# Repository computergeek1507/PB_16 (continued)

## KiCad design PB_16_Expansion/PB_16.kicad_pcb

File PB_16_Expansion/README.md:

# Copyright and Disclaimer
Copyright: Scott Hanson

This documentation describes Open Hardware and is licensed under the CERN Open Hardware License Version 2 - Strongly Reciprocal. (CERN-OHL-S)

You may redistribute and modify this documentation under the terms of the CERN OHL-S-v2 (https://ohwr.org/cern_ohl_s_v2.txt). This documentation is distributed WITHOUT ANY EXPRESS OR IMPLIED WARRANTY, INCLUDING OF MERCHANTABILITY, SATISFACTORY QUALITY AND FITNESS FOR A PARTICULAR PURPOSE. Please see the CERN OHL v2-S for applicable conditions

**Under CERN OHL-S-v2, derivative work must be publicly released as defined in subsection 3.3**

# PB 16 Expansion

The PB16 Expansion is a compact version of the PB16 with only two Expansion Headers. It can be used with any PB16 Family Expansion or Falcon Expansion Boards. There is also an optional [serial breakout board](../PB_16_E682_Serial/README.md) for DMX capability. All the design files are open source and available on github.

## [Part BOM](https://github.com/computergeek1507/PB_16/raw/master/PB_16_Expansion/PB_16.csv)

## [Interactive BOM](https://computergeek1507.github.io/PB_16/PB_16_Expansion/bom/ibom)

----
## Changelog

v5
----
* 2026-02-20
* Add Different Output
* Switched Expansion Header to 24pin Falcon V4 pinout.
* Switched to PB16v2 pinout, use PB16v2 EEPROM

v4
----
* 2022-08-13
* Updated 5V regulator to "Universal" footprint to support different regulators.
* Added Logo

v3
----
* 2020-05-06
* Wiring Routing Updates.

v2
----
* 2020-01-02
* Add Serial Output Header.

v1
----
* 2019-12-31
* First Version.

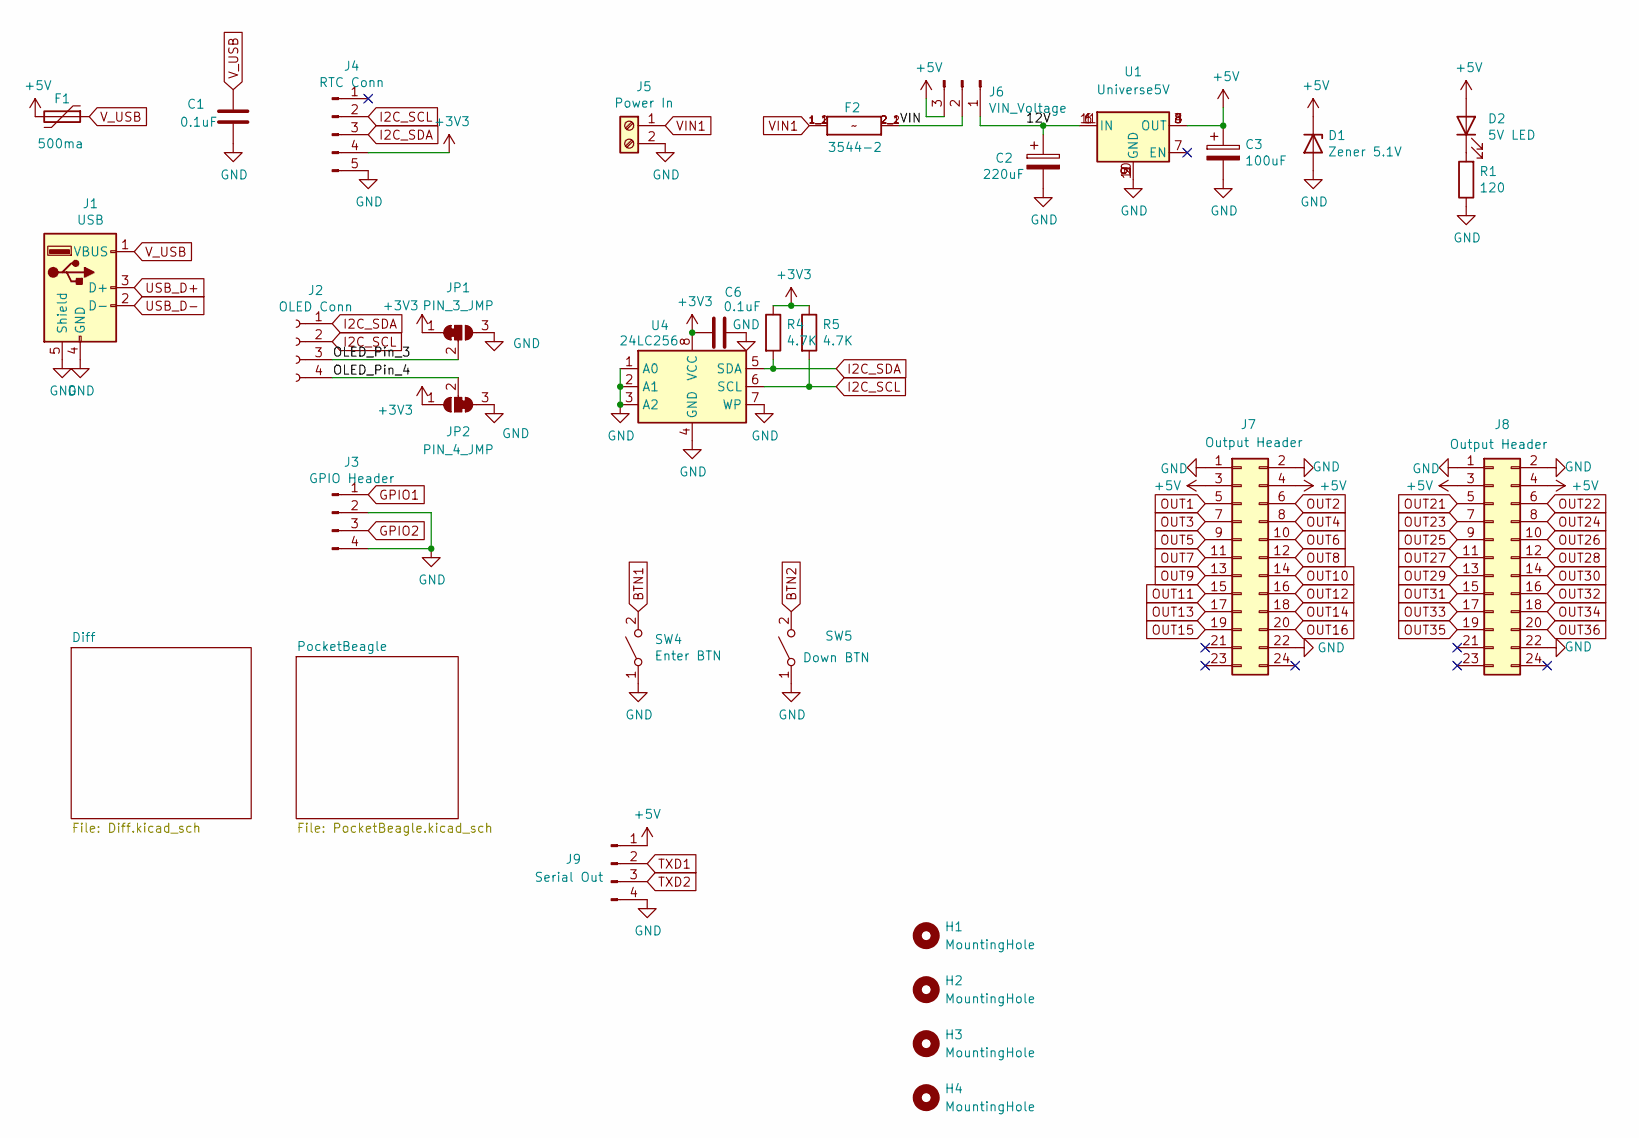
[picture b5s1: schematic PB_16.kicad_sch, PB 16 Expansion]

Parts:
C1, C6: 0.1uF; C_Rect_L7.0mm_W2.0mm_P5.00mm; MPN SR215C104KARTR1; Digi-Key_PN 478-7336-1-ND
C2: 220uF; CP_Radial_D10.0mm_P5.00mm; MPN ECA-1HM221; Digi-Key_PN P5183-ND
C3: 100uF; CP_Radial_D5.0mm_P2.00mm; MPN 16ZLH100MEFC5X11; Digi-Key_PN 1189-1148-ND
D1: Zener 5.1V; D_5W_P10.16mm_Horizontal; MPN 1N5338BRLG; Digi-Key_PN 1N5338BRLGOSCT-ND
D2: 5V LED; LED_D3.0mm; MPN WP3A8GD; Digi-Key_PN 754-1217-ND
F1: 500ma; Fuse_BelFuse_0ZRE0005FF_L8.3mm_W3.8mm; MPN RXEF050-2; Digi-Key_PN RXEF050-2HFCT-ND
F2: 3544-2; FUSE_3544-2; MPN 3544-2; Digi-Key_PN 36-3544-2-ND
H1, H2, H3, H4: MountingHole; MountingHole_3.7mm
J1: USB; USB_A_Molex_105057_Vertical; MPN 1050570001; Digi-Key_PN WM8672-ND
J2: OLED Conn; PinSocket_1x04_P2.54mm_Vertical; MPN PPTC041LFBN-RC; Digi-Key_PN S7002-ND
J3: GPIO Header; JST_XH_B4B-XH-A_1x04_P2.50mm_Vertical; MPN B4B-XH-A(LF)(SN); Digi-Key_PN 455-2249-ND
J4: RTC Conn; PinHeader_1x05_P2.54mm_Vertical; MPN 61300511121; Digi-Key_PN 732-5318-ND
J5: Power In; PHOENIX_MKDS1_2-3.81; MPN 1727010; Digi-Key_PN 277-1947-ND
J6: VIN_Voltage; PinHeader_1x03_P2.54mm_Vertical; MPN 61300311121; Digi-Key_PN 732-5316-ND
J7, J8: Output Header; IDC-Header_2x12_P2.54mm_Vertical; MPN 61202421621; Digi-Key_PN 732-5398-ND
J9: Serial Out; PinHeader_1x04_P2.54mm_Vertical; MPN 61300411121; Digi-Key_PN 732-5317-ND
JP1: PIN_3_JMP; SolderJumper-3_P1mm_Bridged12
JP2: PIN_4_JMP; SolderJumper-3_P1mm_Bridged23
R1: 120; R_Axial_DIN0207_L6.3mm_D2.5mm_P7.62mm_Horizontal; MPN CF14JT120R; Digi-Key_PN CF14JT120RCT-ND
R4, R5: 4.7K; R_Axial_DIN0207_L6.3mm_D2.5mm_P7.62mm_Horizontal; MPN CF14JT4K70; Digi-Key_PN CF14JT4K70CT-ND
SW4: Enter BTN; SW_PUSH_6mm; MPN 1825910-6; Digi-Key_PN 450-1650-ND
SW5: Down BTN; SW_PUSH_6mm; MPN 1825910-6; Digi-Key_PN 450-1650-ND
U1: Universe5V; Universal_5V_Horizontal; MPN OKI-78SR-5/1.5-W36H-C; Digi-Key_PN 811-2692-ND
U4: 24LC256; DIP-8_W7.62mm; MPN FT24C256A-UDR-B; Digi-Key_PN 1219-1052-ND

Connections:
+3V3: C6.2, J4.4, JP1.1 (A), JP2.1 (A), R4.1, R5.1, U4.8 (VCC); also elsewhere on the board
+5V: C3.1, D1.1 (K), D2.2 (A), F1.2, J6.3, J7.3, J7.4, J8.3, J8.4, J9.1, U1.3 (OUT), U1.4 (OUT), U1.8 (OUT); also elsewhere on the board
/12V: C2.1, J6.1, U1.1 (IN), U1.6 (IN), U1.11 (IN)
/OLED_Pin_3: J2.3, JP1.2 (C)
/OLED_Pin_4: J2.4, JP2.2 (C)
/VIN: F2.2_1 (2), F2.2_2 (2), J6.2
BTN1: SW4.2 (B); also elsewhere on the board
BTN2: SW5.2 (B); also elsewhere on the board
GND: C1.2, C2.2, C3.2, C6.1, D1.2 (A), J1.4 (GND), J1.5 (Shield), J3.2, J3.4, J4.5, J5.2, J7.1, J7.2, J7.22, J8.1, J8.2, J8.22, J9.4, JP1.3 (B), JP2.3 (B), R1.1, SW4.1 (A), SW5.1 (A), U1.2 (GND), U1.5 (GND), U1.9 (GND), U1.10 (GND), U4.1 (A0), U4.2 (A1), U4.3 (A2), U4.4 (GND), U4.7 (WP); also elsewhere on the board
GPIO1: J3.1; also elsewhere on the board
GPIO2: J3.3; also elsewhere on the board
I2C_SCL: J2.2, J4.2, R5.2, U4.6 (SCL); also elsewhere on the board
I2C_SDA: J2.1, J4.3, R4.2, U4.5 (SDA); also elsewhere on the board
unnamed: D2.1 (K), R1.2
OUT1: J7.5; also elsewhere on the board
OUT2: J7.6; also elsewhere on the board
OUT3: J7.7; also elsewhere on the board
OUT4: J7.8; also elsewhere on the board
OUT5: J7.9; also elsewhere on the board
OUT6: J7.10; also elsewhere on the board
OUT7: J7.11; also elsewhere on the board
OUT8: J7.12; also elsewhere on the board
OUT9: J7.13; also elsewhere on the board
OUT10: J7.14; also elsewhere on the board
OUT11: J7.15; also elsewhere on the board
OUT12: J7.16; also elsewhere on the board
OUT13: J7.17; also elsewhere on the board
OUT14: J7.18; also elsewhere on the board
OUT15: J7.19; also elsewhere on the board
OUT16: J7.20; also elsewhere on the board
OUT21: J8.5; also elsewhere on the board
OUT22: J8.6; also elsewhere on the board
OUT23: J8.7; also elsewhere on the board
OUT24: J8.8; also elsewhere on the board
OUT25: J8.9; also elsewhere on the board
OUT26: J8.10; also elsewhere on the board
OUT27: J8.11; also elsewhere on the board
OUT28: J8.12; also elsewhere on the board
OUT29: J8.13; also elsewhere on the board
OUT30: J8.14; also elsewhere on the board
OUT31: J8.15; also elsewhere on the board
OUT32: J8.16; also elsewhere on the board
OUT33: J8.17; also elsewhere on the board
OUT34: J8.18; also elsewhere on the board
OUT35: J8.19; also elsewhere on the board
OUT36: J8.20; also elsewhere on the board
TXD1: J9.2; also elsewhere on the board
TXD2: J9.3; also elsewhere on the board
USB_D+: J1.3 (D+); also elsewhere on the board
USB_D-: J1.2 (D-); also elsewhere on the board
VIN1: F2.1_1 (1), F2.1_2 (1), J5.1
V_USB: C1.1, F1.1, J1.1 (VBUS); also elsewhere on the board

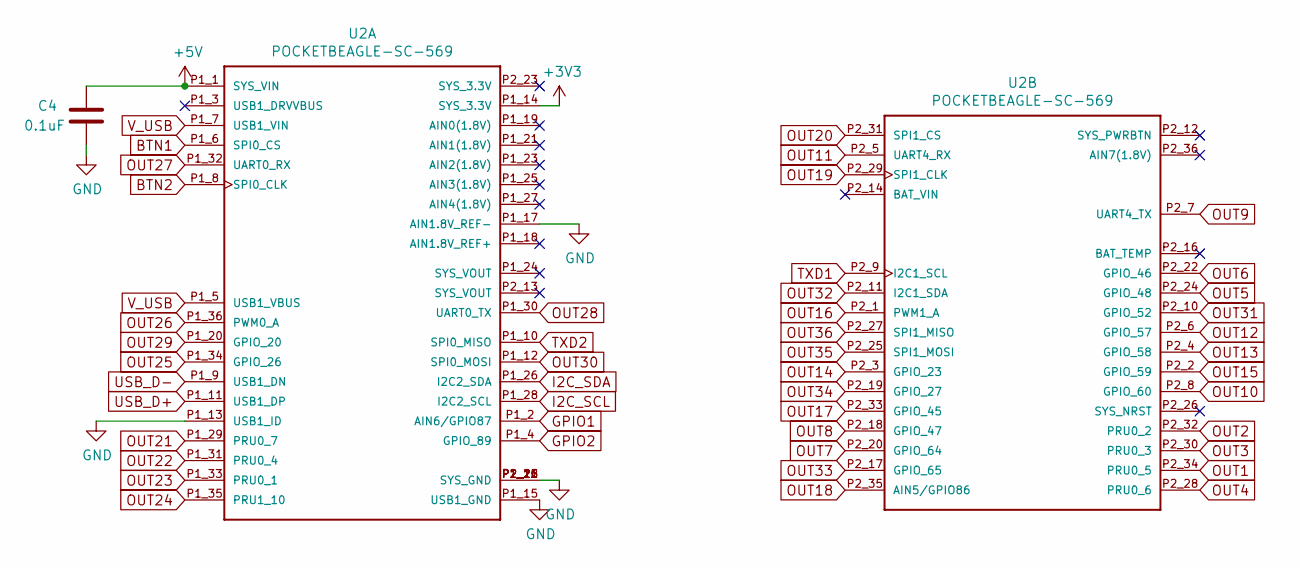
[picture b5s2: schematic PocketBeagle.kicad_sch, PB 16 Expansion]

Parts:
C4: 0.1uF; C_Rect_L7.0mm_W2.0mm_P5.00mm; MPN SR215C104KARTR1; Digi-Key_PN 478-7336-1-ND
U2: POCKETBEAGLE-SC-569; BEAGLE_POCKETBEAGLE-SC-569; MPN POCKETBEAGLE-SC-569; Digi-Key_PN POCKETBEAGLE-SC-569-ND

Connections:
+3V3: U2.P1_14 (SYS_3.3V); also elsewhere on the board
+5V: C4.1, U2.P1_1 (SYS_VIN); also elsewhere on the board
BTN1: U2.P1_6 (SPI0_CS); also elsewhere on the board
BTN2: U2.P1_8 (SPI0_CLK); also elsewhere on the board
GND: C4.2, U2.P1_13 (USB1_ID), U2.P1_15 (USB1_GND), U2.P1_16 (SYS_GND), U2.P1_17 (AIN1.8V_REF-), U2.P1_22 (SYS_GND), U2.P2_15 (SYS_GND), U2.P2_21 (SYS_GND); also elsewhere on the board
GPIO1: U2.P1_2 (AIN6/GPIO87); also elsewhere on the board
GPIO2: U2.P1_4 (GPIO_89); also elsewhere on the board
I2C_SCL: U2.P1_28 (I2C2_SCL); also elsewhere on the board
I2C_SDA: U2.P1_26 (I2C2_SDA); also elsewhere on the board
OUT1: U2.P2_34 (PRU0_5); also elsewhere on the board
OUT2: U2.P2_32 (PRU0_2); also elsewhere on the board
OUT3: U2.P2_30 (PRU0_3); also elsewhere on the board
OUT4: U2.P2_28 (PRU0_6); also elsewhere on the board
OUT5: U2.P2_24 (GPIO_48); also elsewhere on the board
OUT6: U2.P2_22 (GPIO_46); also elsewhere on the board
OUT7: U2.P2_20 (GPIO_64); also elsewhere on the board
OUT8: U2.P2_18 (GPIO_47); also elsewhere on the board
OUT9: U2.P2_7 (UART4_TX); also elsewhere on the board
OUT10: U2.P2_8 (GPIO_60); also elsewhere on the board
OUT11: U2.P2_5 (UART4_RX); also elsewhere on the board
OUT12: U2.P2_6 (GPIO_57); also elsewhere on the board
OUT13: U2.P2_4 (GPIO_58); also elsewhere on the board
OUT14: U2.P2_3 (GPIO_23); also elsewhere on the board
OUT15: U2.P2_2 (GPIO_59); also elsewhere on the board
OUT16: U2.P2_1 (PWM1_A); also elsewhere on the board
OUT17: U2.P2_33 (GPIO_45); also elsewhere on the board
OUT18: U2.P2_35 (AIN5/GPIO86); also elsewhere on the board
OUT19: U2.P2_29 (SPI1_CLK); also elsewhere on the board
OUT20: U2.P2_31 (SPI1_CS); also elsewhere on the board
OUT21: U2.P1_29 (PRU0_7); also elsewhere on the board
OUT22: U2.P1_31 (PRU0_4); also elsewhere on the board
OUT23: U2.P1_33 (PRU0_1); also elsewhere on the board
OUT24: U2.P1_35 (PRU1_10); also elsewhere on the board
OUT25: U2.P1_34 (GPIO_26); also elsewhere on the board
OUT26: U2.P1_36 (PWM0_A); also elsewhere on the board
OUT27: U2.P1_32 (UART0_RX); also elsewhere on the board
OUT28: U2.P1_30 (UART0_TX); also elsewhere on the board
OUT29: U2.P1_20 (GPIO_20); also elsewhere on the board
OUT30: U2.P1_12 (SPI0_MOSI); also elsewhere on the board
OUT31: U2.P2_10 (GPIO_52); also elsewhere on the board
OUT32: U2.P2_11 (I2C1_SDA); also elsewhere on the board
OUT33: U2.P2_17 (GPIO_65); also elsewhere on the board
OUT34: U2.P2_19 (GPIO_27); also elsewhere on the board
OUT35: U2.P2_25 (SPI1_MOSI); also elsewhere on the board
OUT36: U2.P2_27 (SPI1_MISO); also elsewhere on the board
TXD1: U2.P2_9 (I2C1_SCL); also elsewhere on the board
TXD2: U2.P1_10 (SPI0_MISO); also elsewhere on the board
USB_D+: U2.P1_11 (USB1_DP); also elsewhere on the board
USB_D-: U2.P1_9 (USB1_DN); also elsewhere on the board
V_USB: U2.P1_5 (USB1_VBUS), U2.P1_7 (USB1_VIN); also elsewhere on the board

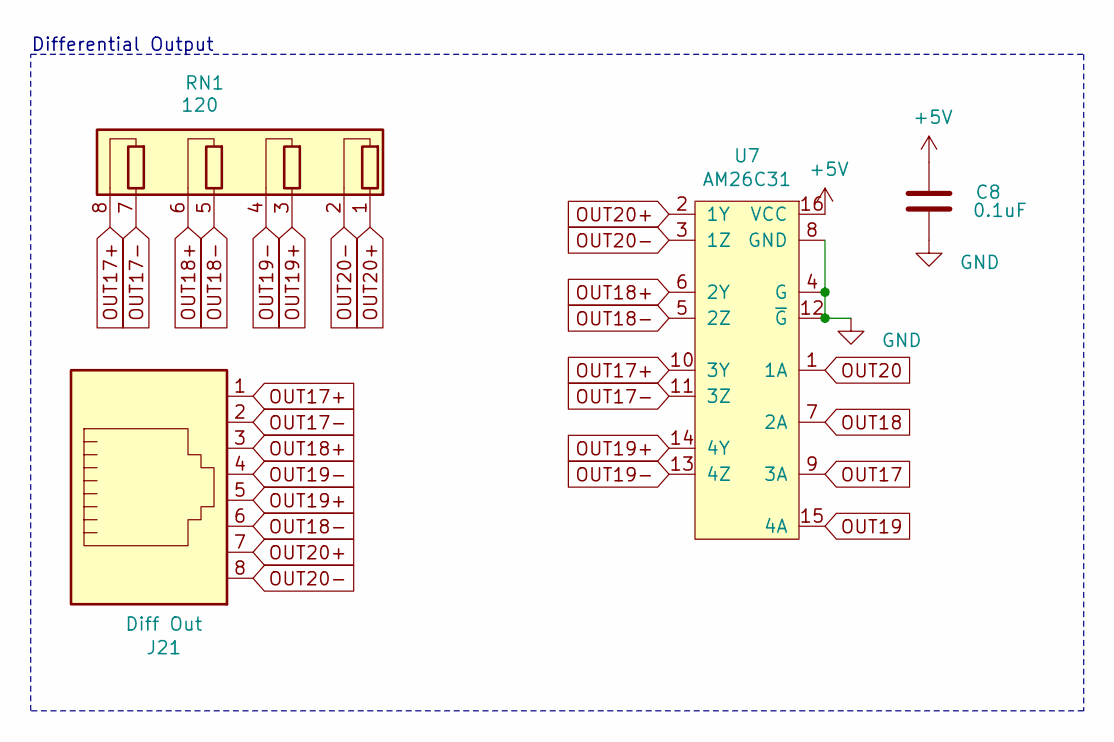
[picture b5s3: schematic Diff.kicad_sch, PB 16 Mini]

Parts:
C8: 0.1uF; C_Rect_L7.0mm_W2.0mm_P5.00mm; MPN SR215C104KARTR1; Digi-Key_PN 478-7336-1-ND
J21: Diff Out; RJ45_Amphenol_54602-x08_Horizontal; MPN X05ADIWA1DY1022; Digi-Key_PN AE10392-ND
RN1: 120; R_Array_SIP8; MPN 4608X-102-121LF; Digikey PN 4608X-2-121LF-ND
U7: AM26C31; DIP-16_W7.62mm; MPN AM26C31IN; Farnell 4975637

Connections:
+5V: C8.1, U7.16 (VCC); also elsewhere on the board
GND: C8.2, U7.4 (G), U7.8 (GND), U7.12 (~G); also elsewhere on the board
OUT17: U7.9 (3A); also elsewhere on the board
OUT17+: J21.1, RN1.8 (R4.2), U7.10 (3Y)
OUT17-: J21.2, RN1.7 (R4.1), U7.11 (3Z)
OUT18: U7.7 (2A); also elsewhere on the board
OUT18+: J21.3, RN1.6 (R3.2), U7.6 (2Y)
OUT18-: J21.6, RN1.5 (R3.1), U7.5 (2Z)
OUT19: U7.15 (4A); also elsewhere on the board
OUT19+: J21.5, RN1.3 (R2.1), U7.14 (4Y)
OUT19-: J21.4, RN1.4 (R2.2), U7.13 (4Z)
OUT20: U7.1 (1A); also elsewhere on the board
OUT20+: J21.7, RN1.1 (R1.1), U7.2 (1Y)
OUT20-: J21.8, RN1.2 (R1.2), U7.3 (1Z)

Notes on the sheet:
Differential Output

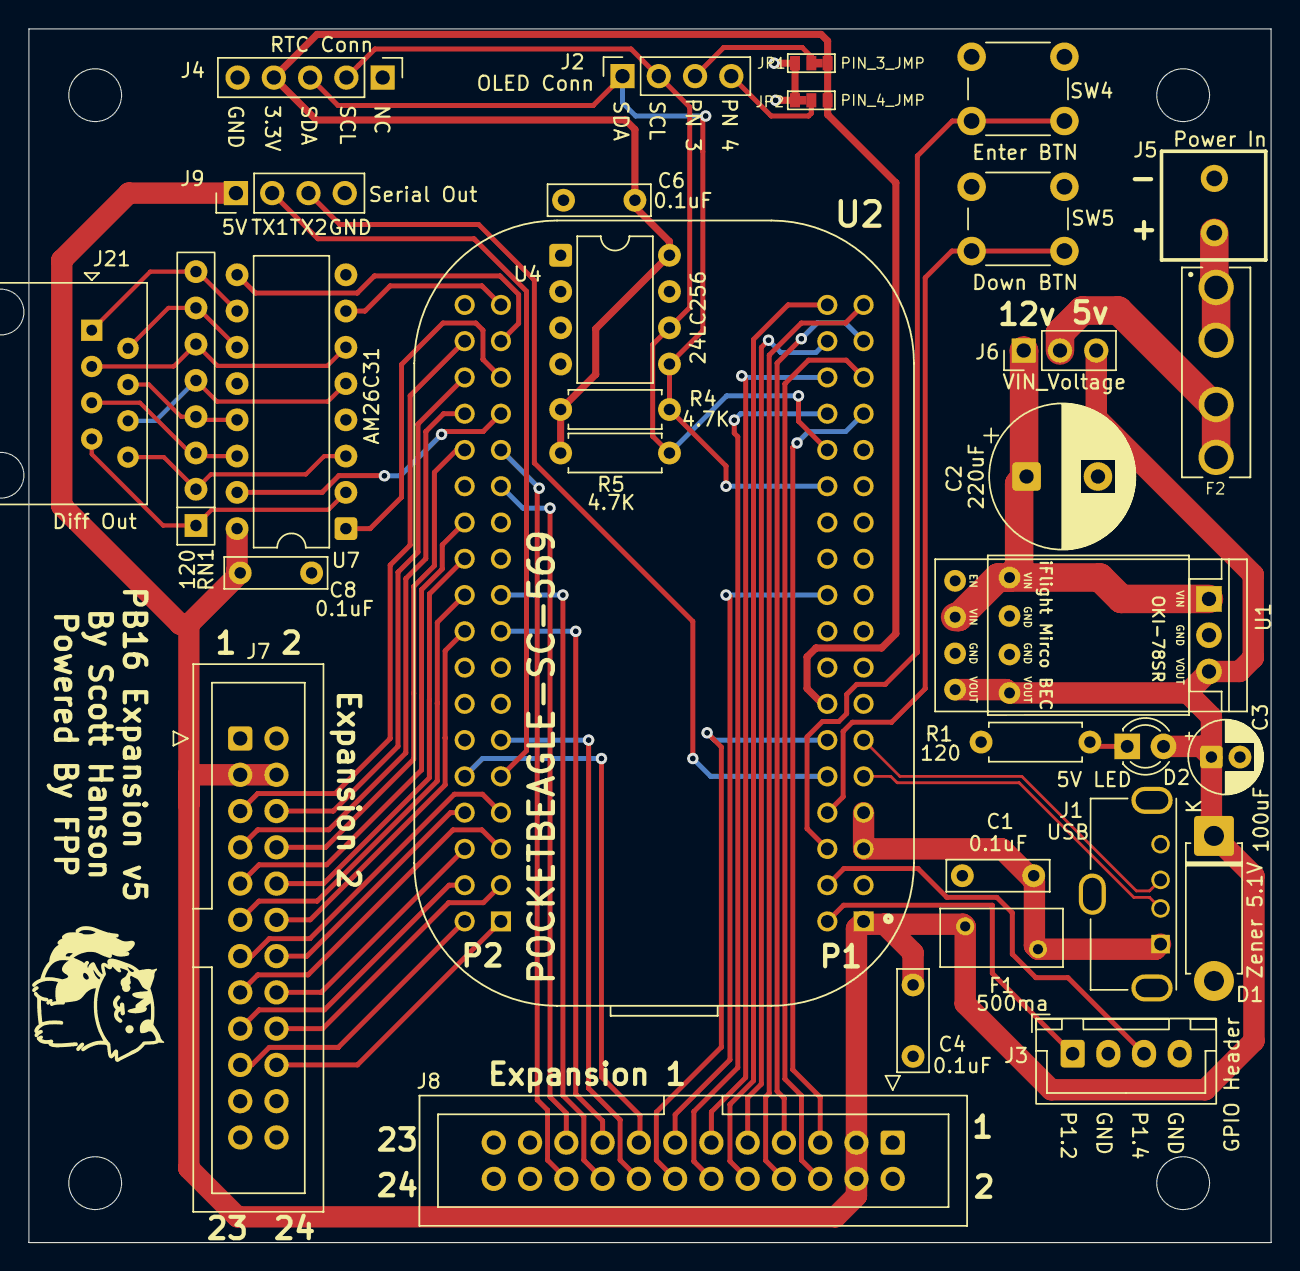
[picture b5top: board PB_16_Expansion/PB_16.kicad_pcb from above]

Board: 2 copper layers, 87.0 x 85.0 mm, 36 parts (0 on the bottom side), 64 nets.

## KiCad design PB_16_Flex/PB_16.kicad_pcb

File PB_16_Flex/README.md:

# Copyright and Disclaimer
Copyright: Scott Hanson

This documentation describes Open Hardware and is licensed under the CERN Open Hardware License Version 2 - Strongly Reciprocal. (CERN-OHL-S)

You may redistribute and modify this documentation under the terms of the CERN OHL-S-v2 (https://ohwr.org/cern_ohl_s_v2.txt). This documentation is distributed WITHOUT ANY EXPRESS OR IMPLIED WARRANTY, INCLUDING OF MERCHANTABILITY, SATISFACTORY QUALITY AND FITNESS FOR A PARTICULAR PURPOSE. Please see the CERN OHL v2-S for applicable conditions

**Under CERN OHL-S-v2, derivative work must be publicly released as defined in subsection 3.3**

# PB 16 Flex

The PB16 Flex is a version of the PB16 for the HolidayCoro Flex System. It can be used with only two flex boards, 32 outputs. All the design files are open source and available on github.

## [Part BOM](https://github.com/computergeek1507/PB_16/raw/master/PB_16_Flex/PB_16_Flex_BOM.ods)

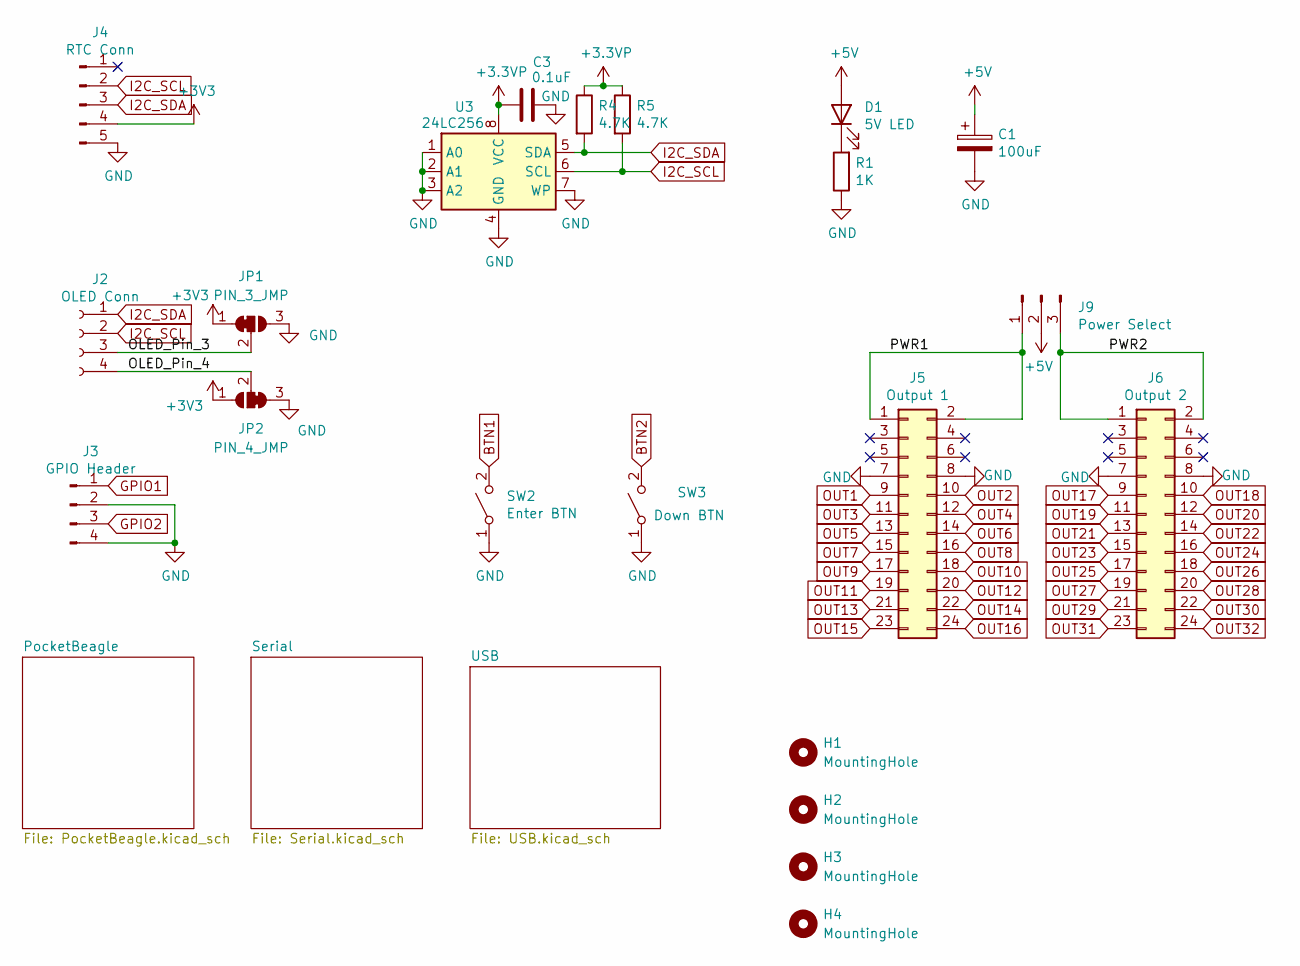
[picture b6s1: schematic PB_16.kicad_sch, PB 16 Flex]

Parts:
C1: 100uF; CP_Elec_6.3x5.4_Nichicon; MPN UWX1C101MCL1GB; Digi-Key_PN 493-2105-1-ND
C3: 0.1uF; C_0805_2012Metric; MPN CL21F104ZBCNNNC; Digi-Key_PN 1276-1007-1-ND
D1: 5V LED; LED_0805_2012Metric_Pad1.15x1.40mm_HandSolder; MPN LTST-C171GKT; Digi-Key_PN 160-1423-1-ND
H1, H2, H3, H4: MountingHole; MountingHole_3.7mm
J2: OLED Conn; PinSocket_1x04_P2.54mm_Vertical; MPN PPTC041LFBN-RC; Digi-Key_PN S7002-ND
J3: GPIO Header; JST_XH_B4B-XH-A_1x04_P2.50mm_Vertical; MPN B4B-XH-A(LF)(SN); Digi-Key_PN 455-2249-ND
J4: RTC Conn; PinHeader_1x05_P2.54mm_Vertical; MPN 61300511121; Digi-Key_PN 732-5318-ND
J5: Output 1; OST_302-S241; MPN 302-S241; Digi-Key_PN ED10525-ND
J6: Output 2; OST_302-S241; MPN 302-S241; Digi-Key_PN ED10525-ND
J9: Power Select; PinHeader_1x03_P2.54mm_Vertical; MPN 61300311121; Digi-Key_PN 732-5316-ND
JP1: PIN_3_JMP; SolderJumper-3_P1mm_Bridged12
JP2: PIN_4_JMP; SolderJumper-3_P1mm_Bridged23
R1: 1K; R_0805_2012Metric; MPN RC0805FR-071KL; Digi-Key_PN 311-1.00KCRCT-ND
R4, R5: 4.7K; R_0805_2012Metric; MPN RC0805JR-074K7L; Digi-Key_PN 311-4.7KARCT-ND
SW2: Enter BTN; SW_PUSH_6mm; MPN 1825910-6; Digi-Key_PN 450-1650-ND
SW3: Down BTN; SW_PUSH_6mm; MPN 1825910-6; Digi-Key_PN 450-1650-ND
U3: 24LC256; SOIC-8_3.9x4.9mm_P1.27mm; MPN 24LC256T-I/SN; Digi-Key_PN 24LC256T-I/SNCT-ND

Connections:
+3.3VP: C3.2, R4.1, R5.1, U3.8 (VCC); also elsewhere on the board
+3V3: J4.4, JP1.1 (A), JP2.1 (A); also elsewhere on the board
+5V: C1.1, D1.2 (A), J9.2; also elsewhere on the board
/OLED_Pin_3: J2.3, JP1.2 (C)
/OLED_Pin_4: J2.4, JP2.2 (C)
/PWR1: J5.1, J5.2, J9.1
/PWR2: J6.1, J6.2, J9.3
BTN1: SW2.2 (B); also elsewhere on the board
BTN2: SW3.2 (B); also elsewhere on the board
GND: C1.2, C3.1, J3.2, J3.4, J4.5, J5.7, J5.8, J6.7, J6.8, JP1.3 (B), JP2.3 (B), R1.1, SW2.1 (A), SW3.1 (A), U3.1 (A0), U3.2 (A1), U3.3 (A2), U3.4 (GND), U3.7 (WP); also elsewhere on the board
GPIO1: J3.1; also elsewhere on the board
GPIO2: J3.3; also elsewhere on the board
I2C_SCL: J2.2, J4.2, R5.2, U3.6 (SCL); also elsewhere on the board
I2C_SDA: J2.1, J4.3, R4.2, U3.5 (SDA); also elsewhere on the board
unnamed: D1.1 (K), R1.2
OUT1: J5.9; also elsewhere on the board
OUT2: J5.10; also elsewhere on the board
OUT3: J5.11; also elsewhere on the board
OUT4: J5.12; also elsewhere on the board
OUT5: J5.13; also elsewhere on the board
OUT6: J5.14; also elsewhere on the board
OUT7: J5.15; also elsewhere on the board
OUT8: J5.16; also elsewhere on the board
OUT9: J5.17; also elsewhere on the board
OUT10: J5.18; also elsewhere on the board
OUT11: J5.19; also elsewhere on the board
OUT12: J5.20; also elsewhere on the board
OUT13: J5.21; also elsewhere on the board
OUT14: J5.22; also elsewhere on the board
OUT15: J5.23; also elsewhere on the board
OUT16: J5.24; also elsewhere on the board
OUT17: J6.9; also elsewhere on the board
OUT18: J6.10; also elsewhere on the board
OUT19: J6.11; also elsewhere on the board
OUT20: J6.12; also elsewhere on the board
OUT21: J6.13; also elsewhere on the board
OUT22: J6.14; also elsewhere on the board
OUT23: J6.15; also elsewhere on the board
OUT24: J6.16; also elsewhere on the board
OUT25: J6.17; also elsewhere on the board
OUT26: J6.18; also elsewhere on the board
OUT27: J6.19; also elsewhere on the board
OUT28: J6.20; also elsewhere on the board
OUT29: J6.21; also elsewhere on the board
OUT30: J6.22; also elsewhere on the board
OUT31: J6.23; also elsewhere on the board
OUT32: J6.24; also elsewhere on the board

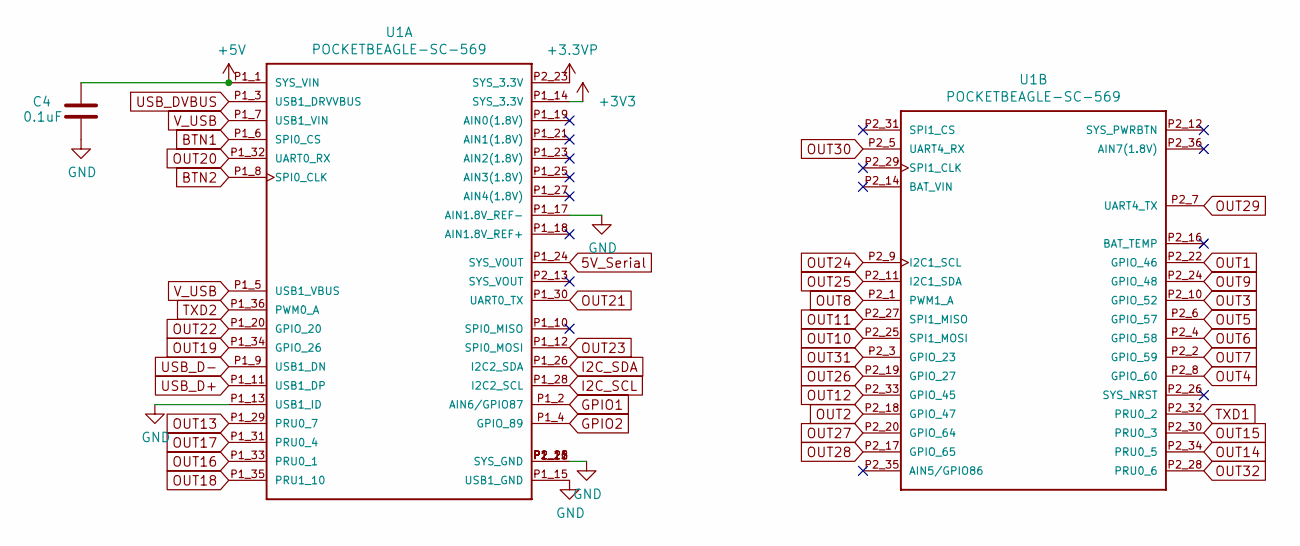
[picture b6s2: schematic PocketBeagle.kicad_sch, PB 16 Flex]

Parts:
C4: 0.1uF; C_0805_2012Metric; MPN CL21F104ZBCNNNC; Digi-Key_PN 1276-1007-1-ND
U1: POCKETBEAGLE-SC-569; BEAGLE_POCKETBEAGLE-SC-569; MPN POCKETBEAGLE-SC-569; Digi-Key_PN POCKETBEAGLE-SC-569-ND

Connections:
5V_Serial: U1.P1_24 (SYS_VOUT); also elsewhere on the board
+3.3VP: U1.P2_23 (SYS_3.3V); also elsewhere on the board
+3V3: U1.P1_14 (SYS_3.3V); also elsewhere on the board
+5V: C4.1, U1.P1_1 (SYS_VIN); also elsewhere on the board
BTN1: U1.P1_6 (SPI0_CS); also elsewhere on the board
BTN2: U1.P1_8 (SPI0_CLK); also elsewhere on the board
GND: C4.2, U1.P1_13 (USB1_ID), U1.P1_15 (USB1_GND), U1.P1_16 (SYS_GND), U1.P1_17 (AIN1.8V_REF-), U1.P1_22 (SYS_GND), U1.P2_15 (SYS_GND), U1.P2_21 (SYS_GND); also elsewhere on the board
GPIO1: U1.P1_2 (AIN6/GPIO87); also elsewhere on the board
GPIO2: U1.P1_4 (GPIO_89); also elsewhere on the board
I2C_SCL: U1.P1_28 (I2C2_SCL); also elsewhere on the board
I2C_SDA: U1.P1_26 (I2C2_SDA); also elsewhere on the board
OUT1: U1.P2_22 (GPIO_46); also elsewhere on the board
OUT2: U1.P2_18 (GPIO_47); also elsewhere on the board
OUT3: U1.P2_10 (GPIO_52); also elsewhere on the board
OUT4: U1.P2_8 (GPIO_60); also elsewhere on the board
OUT5: U1.P2_6 (GPIO_57); also elsewhere on the board
OUT6: U1.P2_4 (GPIO_58); also elsewhere on the board
OUT7: U1.P2_2 (GPIO_59); also elsewhere on the board
OUT8: U1.P2_1 (PWM1_A); also elsewhere on the board
OUT9: U1.P2_24 (GPIO_48); also elsewhere on the board
OUT10: U1.P2_25 (SPI1_MOSI); also elsewhere on the board
OUT11: U1.P2_27 (SPI1_MISO); also elsewhere on the board
OUT12: U1.P2_33 (GPIO_45); also elsewhere on the board
OUT13: U1.P1_29 (PRU0_7); also elsewhere on the board
OUT14: U1.P2_34 (PRU0_5); also elsewhere on the board
OUT15: U1.P2_30 (PRU0_3); also elsewhere on the board
OUT16: U1.P1_33 (PRU0_1); also elsewhere on the board
OUT17: U1.P1_31 (PRU0_4); also elsewhere on the board
OUT18: U1.P1_35 (PRU1_10); also elsewhere on the board
OUT19: U1.P1_34 (GPIO_26); also elsewhere on the board
OUT20: U1.P1_32 (UART0_RX); also elsewhere on the board
OUT21: U1.P1_30 (UART0_TX); also elsewhere on the board
OUT22: U1.P1_20 (GPIO_20); also elsewhere on the board
OUT23: U1.P1_12 (SPI0_MOSI); also elsewhere on the board
OUT24: U1.P2_9 (I2C1_SCL); also elsewhere on the board
OUT25: U1.P2_11 (I2C1_SDA); also elsewhere on the board
OUT26: U1.P2_19 (GPIO_27); also elsewhere on the board
OUT27: U1.P2_20 (GPIO_64); also elsewhere on the board
OUT28: U1.P2_17 (GPIO_65); also elsewhere on the board
OUT29: U1.P2_7 (UART4_TX); also elsewhere on the board
OUT30: U1.P2_5 (UART4_RX); also elsewhere on the board
OUT31: U1.P2_3 (GPIO_23); also elsewhere on the board
OUT32: U1.P2_28 (PRU0_6); also elsewhere on the board
TXD1: U1.P2_32 (PRU0_2); also elsewhere on the board
TXD2: U1.P1_36 (PWM0_A); also elsewhere on the board
USB_D+: U1.P1_11 (USB1_DP); also elsewhere on the board
USB_D-: U1.P1_9 (USB1_DN); also elsewhere on the board
USB_DVBUS: U1.P1_3 (USB1_DRVVBUS); also elsewhere on the board
V_USB: U1.P1_5 (USB1_VBUS), U1.P1_7 (USB1_VIN); also elsewhere on the board

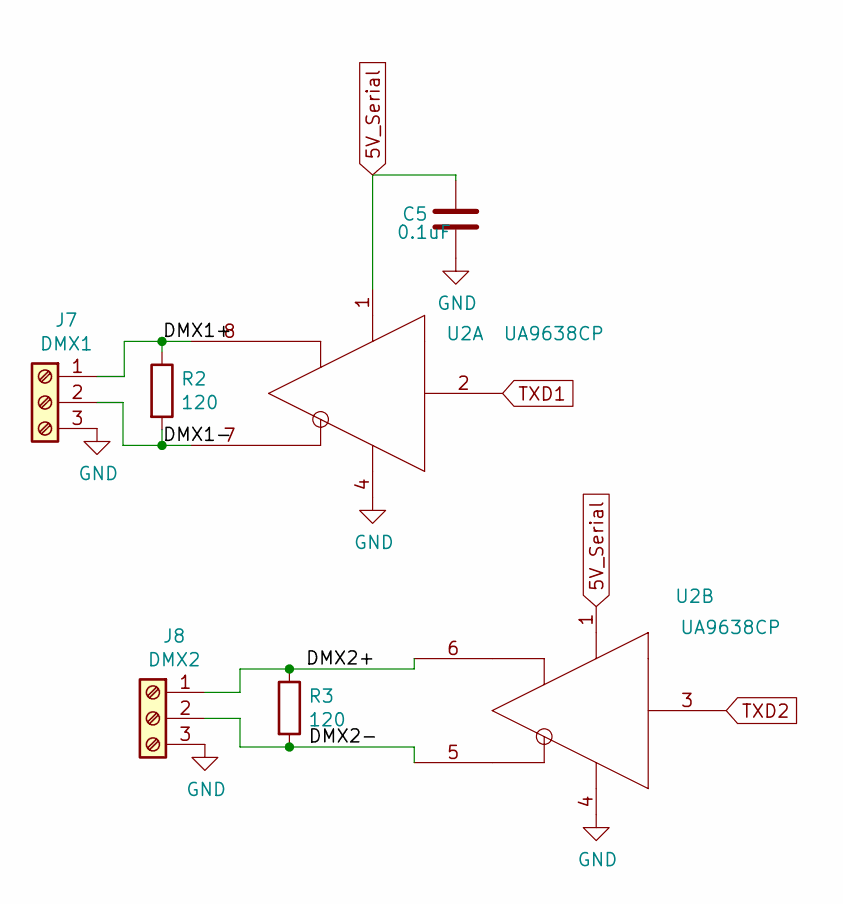
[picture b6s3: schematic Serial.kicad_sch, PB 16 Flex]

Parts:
C5: 0.1uF; C_0805_2012Metric; MPN CL21F104ZBCNNNC; Digi-Key_PN 1276-1007-1-ND
J7: DMX1; PhoenixContact_MCV_1,5_3-G-3.5_1x03_P3.50mm_Vertical; MPN 1843619; Digi-Key_PN 277-5737-ND
J8: DMX2; PhoenixContact_MCV_1,5_3-G-3.5_1x03_P3.50mm_Vertical; MPN 1843619; Digi-Key_PN 277-5737-ND
R2, R3: 120; R_0805_2012Metric; MPN RC0805JR-07120RL; Digi-Key_PN 311-120ARCT-ND
U2: UA9638CP; SOIC-8_3.9x4.9mm_P1.27mm; MPN UA9638CDR; Digi-Key_PN 296-15058-1-ND

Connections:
5V_Serial: C5.1, U2.1 (VCC); also elsewhere on the board
/Serial/DMX1+: J7.1, R2.1, U2.8 (OUTB)
/Serial/DMX1-: J7.2, R2.2, U2.7 (OUTA)
/Serial/DMX2+: J8.1, R3.1, U2.6 (OUTB)
/Serial/DMX2-: J8.2, R3.2, U2.5 (OUTA)
GND: C5.2, J7.3, J8.3, U2.4 (GND); also elsewhere on the board
TXD1: U2.2 (IN); also elsewhere on the board
TXD2: U2.3 (IN); also elsewhere on the board

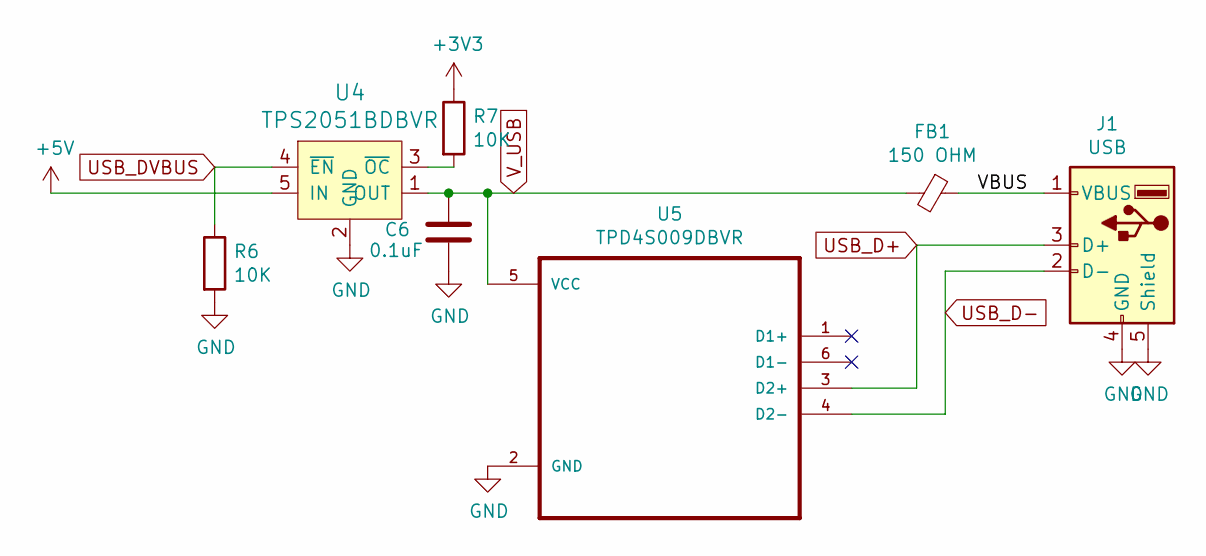
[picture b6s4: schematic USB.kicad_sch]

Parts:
C6: 0.1uF; C_0805_2012Metric; MPN CL21F104ZBCNNNC; Digi-Key_PN 1276-1007-1-ND
FB1: 150 OHM; L_0805_2012Metric; MPN MU2029-151Y; Digi-Key_PN MU2029-151YCT-ND
J1: USB; USB_A_Stewart_SS-52100-001_Horizontal; MPN SS-52100-001; Digi-Key_PN 380-1412-ND
R6, R7: 10K; R_0805_2012Metric; MPN RNCP0805FTD10K0; Digi-Key_PN RNCP0805FTD10K0CT-ND
U4: TPS2051BDBVR; SOT-753; MPN TPS2051BDBVR; Digi-Key_PN 296-21265-1-ND
U5: TPD4S009DBVR; SOT-23-6_Handsoldering; MPN TPD4S009DBVR; Digi-Key_PN 296-23749-1-ND

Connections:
+3V3: R7.1; also elsewhere on the board
+5V: U4.5 (IN); also elsewhere on the board
/USB/VBUS: FB1.1, J1.1 (VBUS)
GND: C6.2, J1.4 (GND), J1.5 (Shield), R6.2, U4.2 (GND), U5.2 (GND); also elsewhere on the board
unnamed: R7.2, U4.3 (~OC)
USB_D+: J1.3 (D+), U5.3 (D2+); also elsewhere on the board
USB_D-: J1.2 (D-), U5.4 (D2-); also elsewhere on the board
USB_DVBUS: R6.1, U4.4 (~EN); also elsewhere on the board
V_USB: C6.1, FB1.2, U4.1 (OUT), U5.5 (VCC); also elsewhere on the board

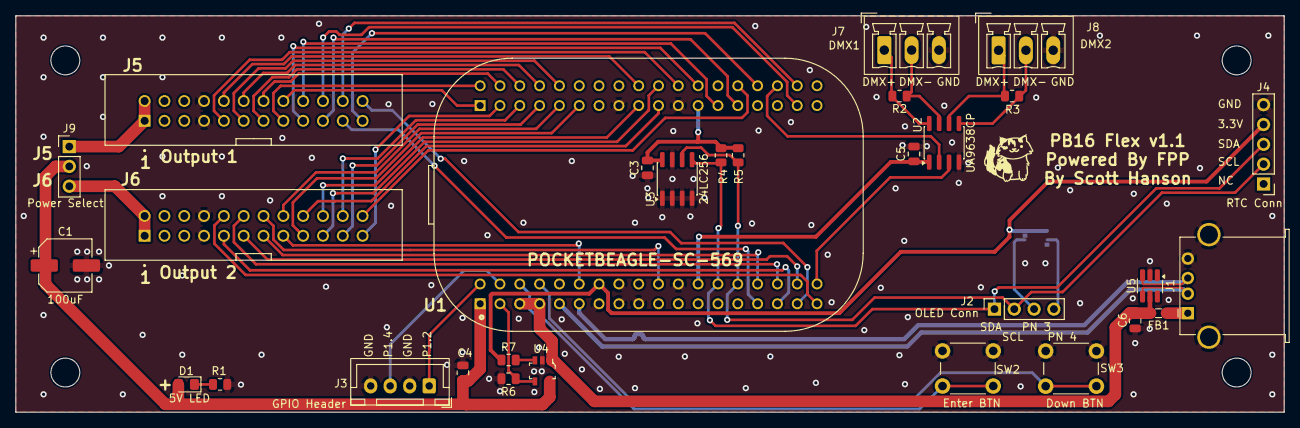
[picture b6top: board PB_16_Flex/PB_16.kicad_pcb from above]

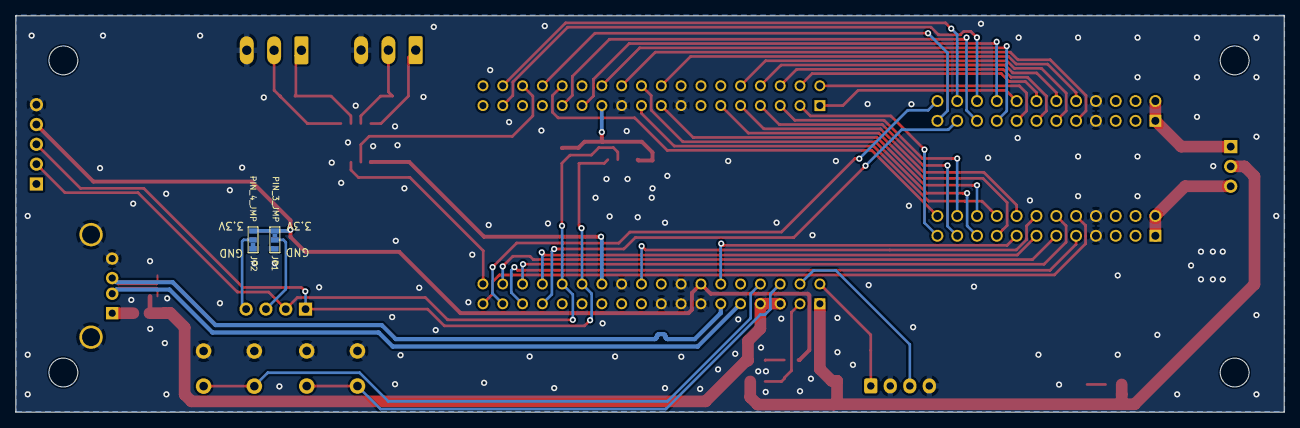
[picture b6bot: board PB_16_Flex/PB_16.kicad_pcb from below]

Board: 2 copper layers, 162.6 x 50.8 mm, 36 parts (2 on the bottom side), 60 nets.

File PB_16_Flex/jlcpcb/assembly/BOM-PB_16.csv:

Comment,Designator,Footprint,LCSC
100uF,C1,CP_Elec_6.3x5.4_Nichicon,
5V LED,D1,LED_0805_2012Metric_Pad1.15x1.40mm_HandSolder,
OLED Conn,J2,PinSocket_1x04_P2.54mm_Vertical,
GPIO Header,J3,JST_XH_B4B-XH-A_1x04_P2.50mm_Vertical,
RTC Conn,J4,PinHeader_1x05_P2.54mm_Vertical,
OLED Select,SW1,SW_CuK_JS202011CQN_DPDT_Straight,
4.7K,R4,R_0805_2012Metric_Pad1.15x1.40mm_HandSolder,
4.7K,R5,R_0805_2012Metric_Pad1.15x1.40mm_HandSolder,
0.1uF,C3,C_0805_2012Metric_Pad1.15x1.40mm_HandSolder,
24LC256,U3,SOIC-8_3.9x4.9mm_P1.27mm,
Down BTN,SW3,SW_PUSH_6mm,
1K,R1,R_0805_2012Metric_Pad1.15x1.40mm_HandSolder,
Enter BTN,SW2,SW_PUSH_6mm,
DMX1,J7,"PhoenixContact_MCV_1,5_3-G-3.5_1x03_P3.50mm_Vertical",
Output 2,J6,OST_302-S241,
Output 1,J5,OST_302-S241,
120,R3,R_0805_2012Metric_Pad1.15x1.40mm_HandSolder,
0.1uF,C4,C_0805_2012Metric_Pad1.15x1.40mm_HandSolder,
Power Select,J9,PinHeader_1x03_P2.54mm_Vertical,
UA9638CP,U2,SOIC-8_3.9x4.9mm_P1.27mm,
0.1uF,C5,C_0805_2012Metric_Pad1.15x1.40mm_HandSolder,
DMX2,J8,"PhoenixContact_MCV_1,5_3-G-3.5_1x03_P3.50mm_Vertical",
0.1uF,C6,C_0805_2012Metric_Pad1.15x1.40mm_HandSolder,
150 OHM,FB1,L_0805_2012Metric_Pad1.15x1.40mm_HandSolder,
USB,J1,USB_A_Stewart_SS-52100-001_Horizontal,
TPS2051BDBVR,U4,SOT-753,
10K,R6,R_0805_2012Metric_Pad1.15x1.40mm_HandSolder,
120,R2,R_0805_2012Metric_Pad1.15x1.40mm_HandSolder,
10K,R7,R_0805_2012Metric_Pad1.15x1.40mm_HandSolder,
POCKETBEAGLE-SC-569,U1,BEAGLE_POCKETBEAGLE-SC-569,
TPD4S009DBVR,U5,SOT-23-6_Handsoldering,
